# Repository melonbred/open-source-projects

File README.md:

# open-source-projects

**Repository for projects by MelonBred**

This is a repository for all open-sourced or available files for my projects. PCBs will typically have their own repository linked in the table below. Everything else will probably be found here in this repository but still linked in the tables below.

---

## Keyboards

| <div style="width:100px">_Project_</div>                                                 | _Description_                                                                                 | _Available Files_           | Image                                                                                                      |
| ---------------------------------------------------------------------------------------- | --------------------------------------------------------------------------------------------- | --------------------------- | ---------------------------------------------------------------------------------------------------------- |
| [MBLB](https://github.com/melonbred/open-source-projects/tree/main/keyboards/mblb)       | 12.5u main cluster + macro column 40% keyboard, rotary encoder support, STM32 microprocessor. | KiCAD, Gerbers, .dxf, .step |                                      |
| [MB-44](https://github.com/melonbred/open-source-projects/tree/main/keyboards/mb44)      | The MB-44 is a 12.75u layout with a fun 65%-esque blocker separating the arrow cluster.       | KiCAD, Gerbers, .dxf, .step |                                        |
| [Pegasus](https://github.com/melonbred/open-source-projects/tree/main/keyboards/pegasus) | 12.75u 40% keyboard with 0.75u "WKL" blockers                                                 | KiCAD, Gerbers, .step, .fbx |                                     |
| [MB-44 v2](https://github.com/melonbred/mb44v2/tree/main)                                | Update to the MB-44 with refreshed case and PCB.                                              | KiCAD, Gerbers, .dxf, .fbx  |  |

## PCBs

| _Project_                                                         | _Description_                                                                                                                              | _Available Files_     | Image                                                                                                        |
| ----------------------------------------------------------------- | ------------------------------------------------------------------------------------------------------------------------------------------ | --------------------- | ------------------------------------------------------------------------------------------------------------ |
| [Program Yoink!](https://github.com/melonbred/program-yoink)      | 12u main cluster with exploded arrows and macro columm                                                                                     | KiCAD, Gerbers        |    |
| [SPM1800](https://github.com/melonbred/SPM1800)                   | Southpaw compact mini 1800                                                                                                                 | KiCAD, Gerbers        |     |
| [kb-daughterboard](https://github.com/melonbred/kb-daughterboard) | USB-C daughterboard with ESD, overcurrent and overvoltage protection. 2 versions available - USB-C receptacle flush with PCB and protruded | KiCAD, Gerbers, .step |  |

## Miscellaneous

| _Project_                                                                                                  | _Description_                                       | _Available Files_ | Image                                                                                                                         |
| ---------------------------------------------------------------------------------------------------------- | --------------------------------------------------- | ----------------- | ----------------------------------------------------------------------------------------------------------------------------- |
| [MB-44 Plates](https://github.com/melonbred/open-source-projects/tree/main/miscellaneous/mb44-plate-files) | Plate files for the MB-44 keyboard                  | .dxf              |
| [Encoder Knob](https://github.com/melonbred/open-source-projects/tree/main/miscellaneous/encoder-knobs)    | Generic knob that fits EC11 encoders. 3d printable. | .step, .stl       |  |

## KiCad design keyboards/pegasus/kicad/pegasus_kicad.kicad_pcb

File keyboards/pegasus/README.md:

# pegasus

## Introduction

The Pegasus is a 12.75u layout with 0.75u "WKL" blockers.

Group buy for this keyboard ran through [P3D Store](https://p3dstore.com/) on May 21st, 2022, and all group buy orders were shipped in January, 2023. Extra units were sold on January 25th, 2023. The project was successfully completed in February, 2023.

An album of builds done by the community can be found [here](https://imgur.com/a/YTEutIl).

This repository includes kicad directory, pcb production files and case files in STEP and FBX formats.

## Features

- 12.75u layout 0.75u "WKL" blockers.
- Big bar and split bar layout options.
- Rotary encoder support.
- PCB powered by an Atmega32u4 and Unified C3 daughterboard (type-c and ESD protection) running QMK.

### KLE

## Production

Please note that the pcb production files were prepared with JLCPCB's SMT assembly in mind. Should you deicide to proceed with a different manufacturer, the Bill of Materials (BOM) and position files may need to be modified.

Vial firmware source can be found [here](https://github.com/melonbred/vial-qmk/tree/kb-pegasus/keyboards/pegasus).

Firmware is also accessible through [QMK Configurator](https://config.qmk.fm/#/pegasus/LAYOUT_default).

## Acknowledgment

This project would not have taken off without the tremendous support from the 40% keyboard community. Please feel free to join the 40% keyboard [Discord](https://discord.com/invite/40percent) server to follow up-and-coming project and join the conversations.

Thanks to [P3D Store](https://p3dstore.com/) for their support and fullfillment of the group buy!!

Thanks to all the friends that helped along the way. Y'all are the best.

This project uses repositories made available by [ai03](https://github.com/ai03-2725/).

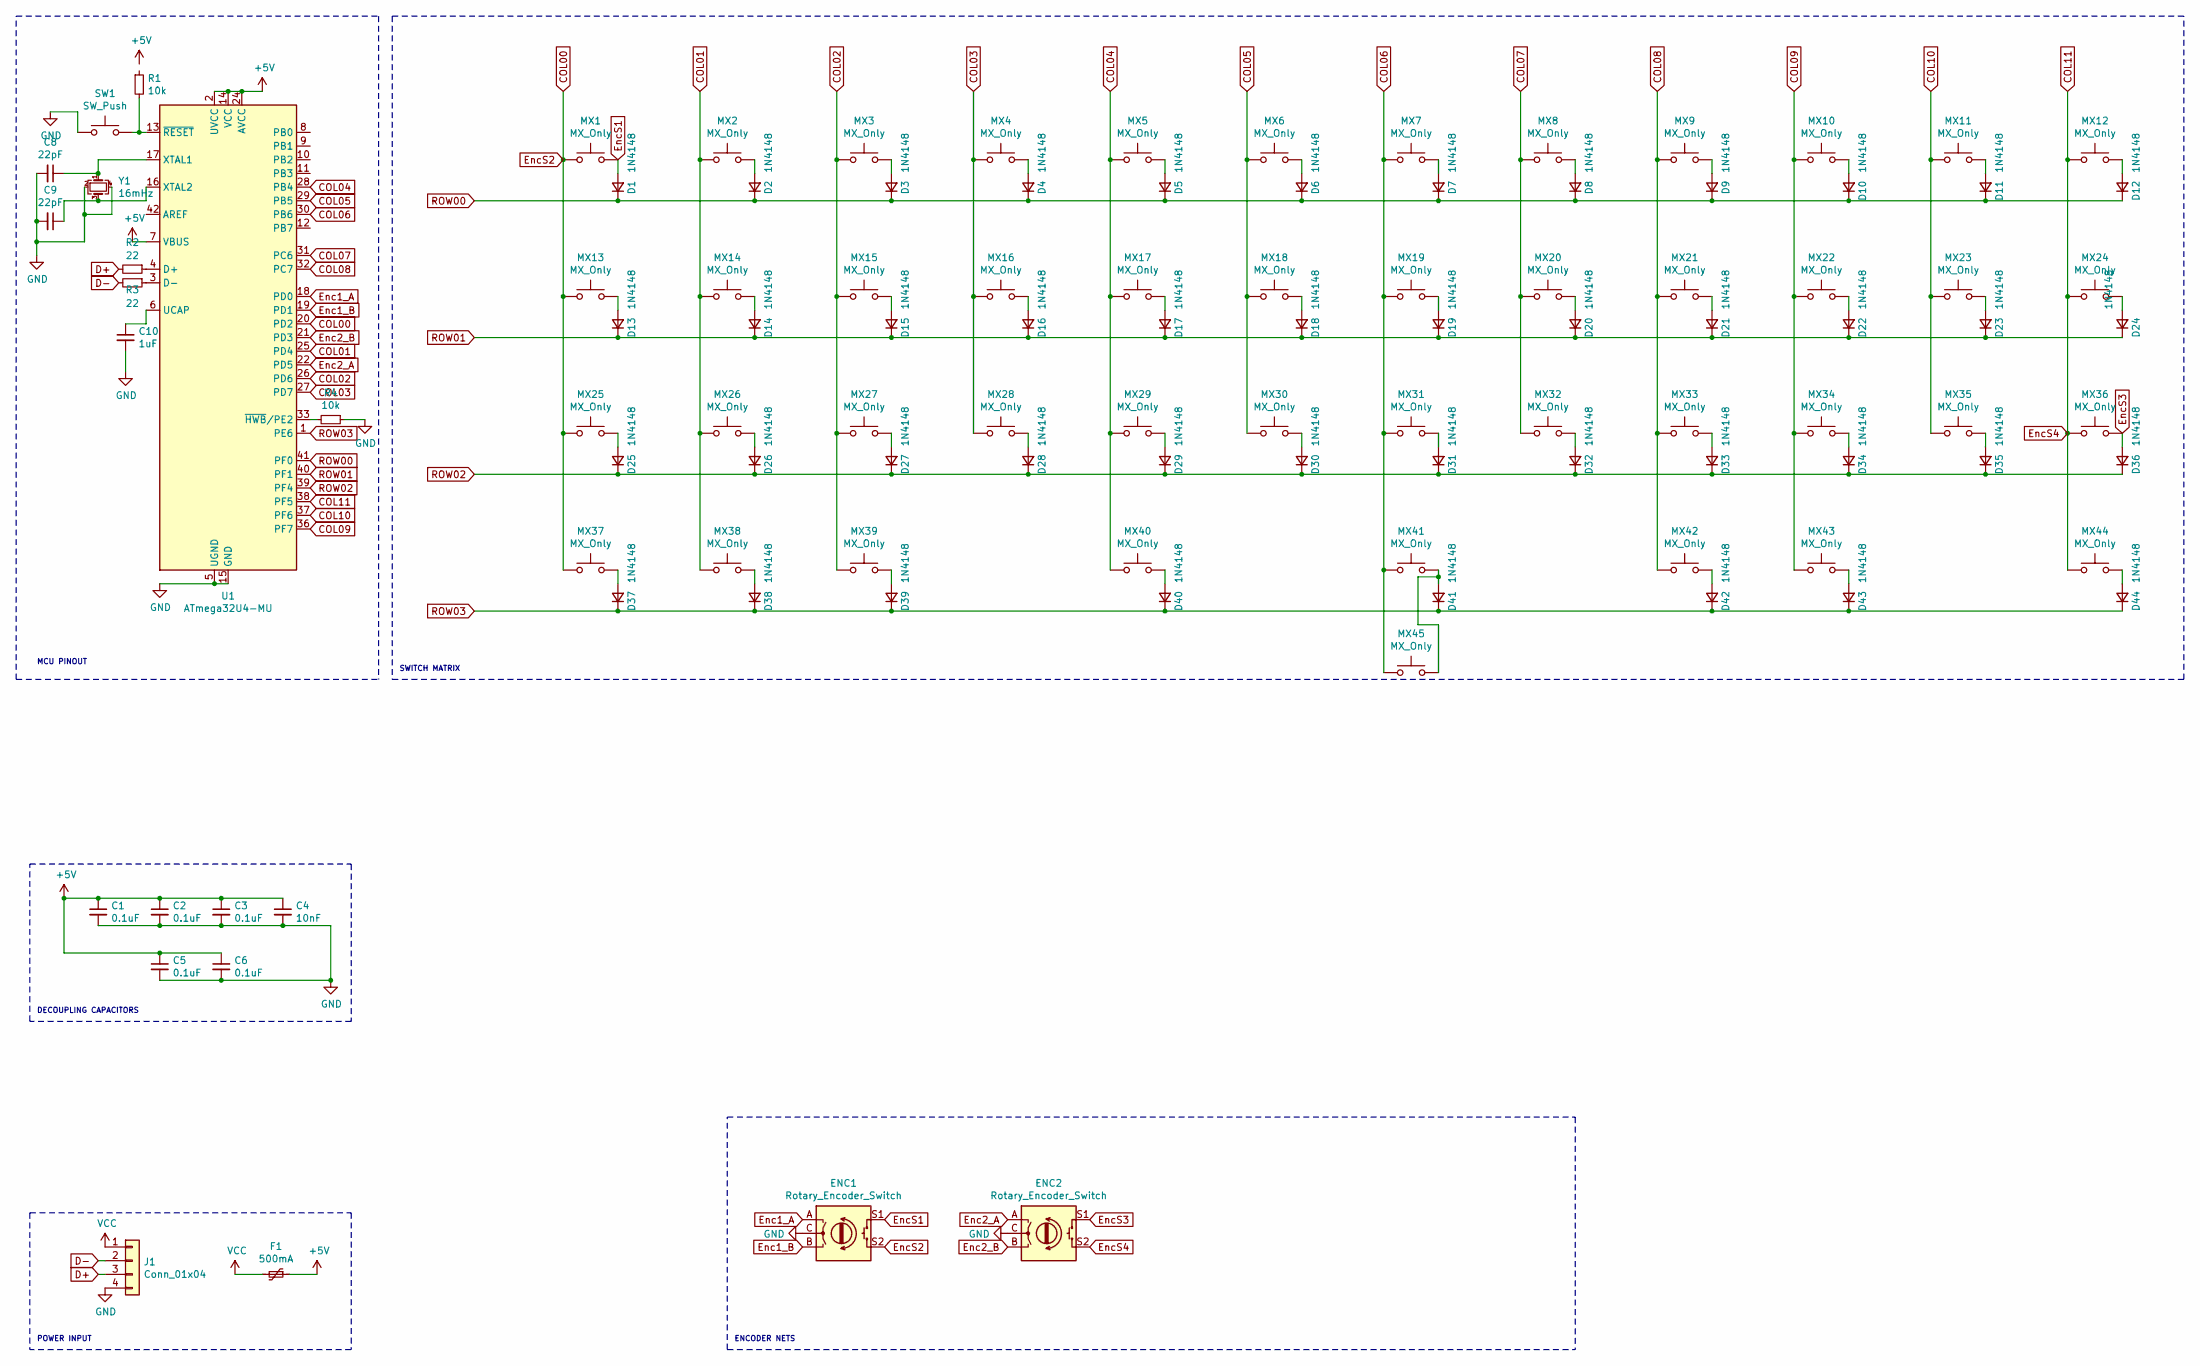
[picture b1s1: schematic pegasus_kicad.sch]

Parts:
C1, C2, C3: 0.1uF; C_0603_1608Metric; LCSC Part # C28233
C4: 10nF; C_0603_1608Metric; LCSC Part # C1710
C5, C6: 0.1uF; C_0603_1608Metric; LCSC Part # C87998
C8, C9: 22pF; C_0603_1608Metric
C10: 1uF; C_0603_1608Metric
D1, D2, D3, D4, D5, D6, D7, D8, D9, D10, D11, D12, D13, D14, D15, D16, D17, D18, D19, D20, D21, D22, D23, D24, D25, D26, D27, D28, D29, D30, D31, D32, D33, D34, D35, D36, D37, D38, D39, D40, D41, D42, D43, D44: 1N4148; D_SOD-123; LCSC Part # C402213
ENC1, ENC2: Rotary_Encoder_Switch; RotaryEncoder_Alps_EC11E-Switch_Vertical_H20mm
F1: 500mA; Fuse_1206_3216Metric; LCSC Part # C70069
J1: Conn_01x04; JST-SR-4; LCSC Part # C160404
MX1, MX2, MX3, MX4, MX5, MX6, MX7, MX8, MX9, MX10, MX11, MX14, MX15, MX16, MX17, MX18, MX19, MX20, MX21, MX22, MX23, MX26, MX27, MX28, MX29, MX30, MX31, MX32, MX33, MX34, MX35, MX36, MX39, MX42: MX_Only; MXOnly-1U-NoLED
MX12, MX25: MX_Only; MXOnly-1.75U-NoLED
MX13, MX37, MX38, MX43, MX44: MX_Only; MXOnly-1.25U-NoLED
MX24: MX_Only; MXOnly-1.5U-NoLED
MX40: MX_Only; MXOnly-2U-ReversedStabilizers-NoLED
MX41: MX_Only; MXOnly-2.25U-ReversedStabilizers-NoLED
MX45: MX_Only; MXOnly-6.25U-ReversedStabilizers-NoLED
R1, R4: 10k; R_0603_1608Metric
R2, R3: 22; R_0603_1608Metric
SW1: SW_Push; SKQG-1155865
U1: ATmega32U4-MU; QFN-44-1EP_7x7mm_P0.5mm_EP5.2x5.2mm
Y1: 16mHz; Crystal_SMD_3225-4Pin_3.2x2.5mm

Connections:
+5V: C1.1, C2.1, C3.1, C4.1, C5.1, C6.1, F1.1, U1.2 (UVCC), U1.7 (VBUS), U1.14 (VCC), U1.24 (AVCC), U1.34 (VCC), U1.44 (AVCC)
COL00: ENC1.S2, MX1.1, MX13.1, MX25.1, MX37.1, U1.20 (PD2)
COL01: MX2.1, MX14.1, MX26.1, MX38.1, U1.25 (PD4)
COL02: MX3.1, MX15.1, MX27.1, MX39.1, U1.26 (PD6)
COL03: MX4.1, MX16.1, MX28.1, U1.27 (PD7)
COL04: MX5.1, MX17.1, MX29.1, MX40.1, U1.28 (PB4)
COL05: MX6.1, MX18.1, MX30.1, U1.29 (PB5)
COL06: MX7.1, MX19.1, MX31.1, MX41.1, MX45.1, U1.30 (PB6)
COL07: MX8.1, MX20.1, MX32.1, U1.31 (PC6)
COL08: MX9.1, MX21.1, MX33.1, MX42.1, U1.32 (PC7)
COL09: MX10.1, MX22.1, MX34.1, MX43.1, U1.36 (PF7)
COL10: MX11.1, MX23.1, MX35.1, U1.37 (PF6)
COL11: ENC2.S2, MX12.1, MX24.1, MX36.1, MX44.1, U1.38 (PF5)
D+: J1.3, R2.2
D-: J1.2, R3.2
Enc1_A: ENC1.A, U1.18 (PD0)
Enc1_B: ENC1.B, U1.19 (PD1)
Enc2_A: ENC2.A, U1.22 (PD5)
Enc2_B: ENC2.B, U1.21 (PD3)
EncS1: D1.2 (A), ENC1.S1, MX1.2
EncS3: D36.2 (A), ENC2.S1, MX36.2
GND: C1.2, C2.2, C3.2, C4.2, C5.2, C6.2, C8.2, C9.2, C10.2, ENC1.C, ENC2.C, J1.4, R4.1, SW1.1, U1.5 (UGND), U1.15 (GND), U1.23 (GND), U1.35 (GND), U1.43 (GND), U1.45 (GND), Y1.2, Y1.4
unnamed: C8.1, U1.17 (XTAL1), Y1.1
unnamed: C9.1, U1.16 (XTAL2), Y1.3
unnamed: C10.1, U1.6 (UCAP)
unnamed: D2.2 (A), MX2.2
unnamed: D3.2 (A), MX3.2
unnamed: D4.2 (A), MX4.2
unnamed: D5.2 (A), MX5.2
unnamed: D6.2 (A), MX6.2
unnamed: D7.2 (A), MX7.2
unnamed: D8.2 (A), MX8.2
unnamed: D9.2 (A), MX9.2
unnamed: D10.2 (A), MX10.2
unnamed: D11.2 (A), MX11.2
unnamed: D12.2 (A), MX12.2
unnamed: D13.2 (A), MX13.2
unnamed: D14.2 (A), MX14.2
unnamed: D15.2 (A), MX15.2
unnamed: D16.2 (A), MX16.2
unnamed: D17.2 (A), MX17.2
unnamed: D18.2 (A), MX18.2
unnamed: D19.2 (A), MX19.2
unnamed: D20.2 (A), MX20.2
unnamed: D21.2 (A), MX21.2
unnamed: D22.2 (A), MX22.2
unnamed: D23.2 (A), MX23.2
unnamed: D24.2 (A), MX24.2
unnamed: D25.2 (A), MX25.2
unnamed: D26.2 (A), MX26.2
unnamed: D27.2 (A), MX27.2
unnamed: D28.2 (A), MX28.2
unnamed: D29.2 (A), MX29.2
unnamed: D30.2 (A), MX30.2
unnamed: D31.2 (A), MX31.2
unnamed: D32.2 (A), MX32.2
unnamed: D33.2 (A), MX33.2
unnamed: D34.2 (A), MX34.2
unnamed: D35.2 (A), MX35.2
unnamed: D37.2 (A), MX37.2
unnamed: D38.2 (A), MX38.2
unnamed: D39.2 (A), MX39.2
unnamed: D40.2 (A), MX40.2
unnamed: D41.2 (A), MX41.2, MX45.2
unnamed: D42.2 (A), MX42.2
unnamed: D43.2 (A), MX43.2
unnamed: D44.2 (A), MX44.2
unnamed: R1.2, SW1.2, U1.13 (~RESET)
unnamed: R2.1, U1.4 (D+)
unnamed: R3.1, U1.3 (D-)
unnamed: R4.2, U1.33 (~HWB~/PE2)
ROW00: D1.1 (K), D2.1 (K), D3.1 (K), D4.1 (K), D5.1 (K), D6.1 (K), D7.1 (K), D8.1 (K), D9.1 (K), D10.1 (K), D11.1 (K), D12.1 (K), U1.41 (PF0)
ROW01: D13.1 (K), D14.1 (K), D15.1 (K), D16.1 (K), D17.1 (K), D18.1 (K), D19.1 (K), D20.1 (K), D21.1 (K), D22.1 (K), D23.1 (K), D24.1 (K), U1.40 (PF1)
ROW02: D25.1 (K), D26.1 (K), D27.1 (K), D28.1 (K), D29.1 (K), D30.1 (K), D31.1 (K), D32.1 (K), D33.1 (K), D34.1 (K), D35.1 (K), D36.1 (K), U1.39 (PF4)
ROW03: D37.1 (K), D38.1 (K), D39.1 (K), D40.1 (K), D41.1 (K), D42.1 (K), D43.1 (K), D44.1 (K), U1.1 (PE6)
VCC: F1.2, J1.1

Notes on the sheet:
DECOUPLING CAPACITORS
POWER INPUT
ENCODER NETS
SWITCH MATRIX
MCU PINOUT

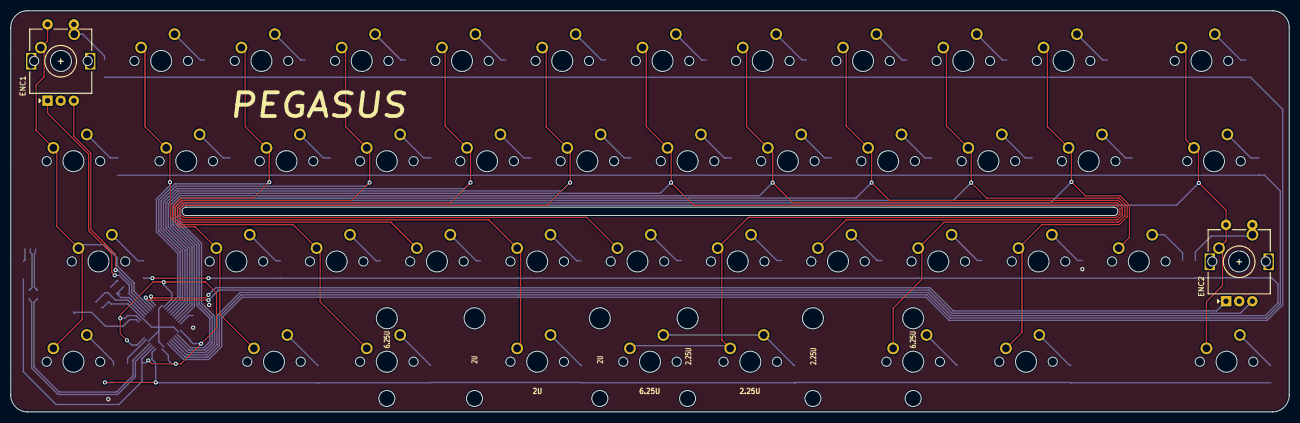
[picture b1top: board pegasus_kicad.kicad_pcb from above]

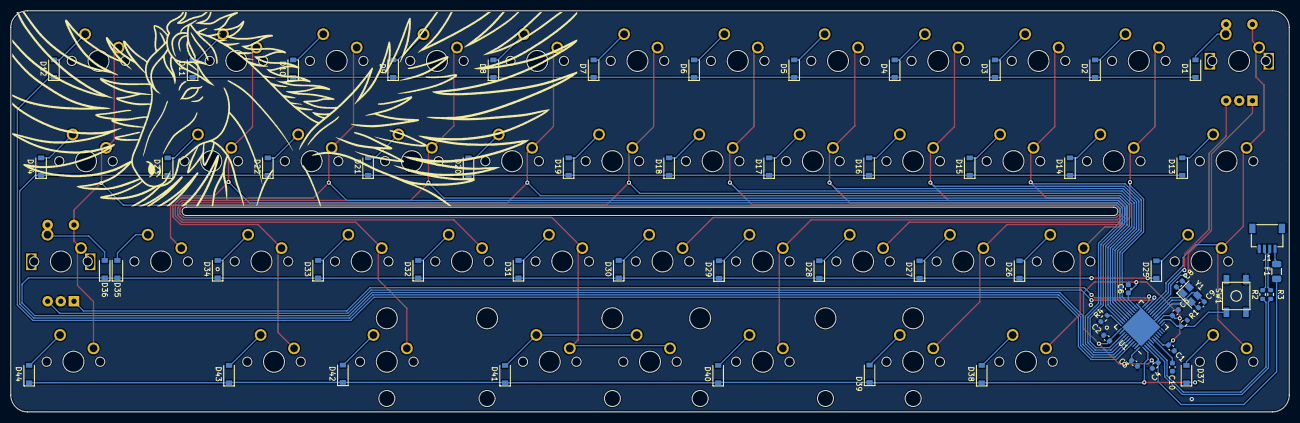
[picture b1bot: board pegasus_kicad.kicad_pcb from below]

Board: 2 copper layers, 242.9 x 76.2 mm, 109 parts (62 on the bottom side), 76 nets.

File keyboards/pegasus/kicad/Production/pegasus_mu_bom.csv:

Designator,Quantity,Value,Footprint,LCSC #
U1,1,ATmega32U4-MU,QFN-44-1EP_7x7mm_P0.5mm_EP5.2x5.2mm,C112161
"R4,R1",2,10k,R_0603_1608Metric,C25804
"D42,D25,D44,D43,D41,D40,D39,D38,D37,D36,D35,D34,D33,D32,D31,D30,D29,D28,D27,D26,D24,D23,D22,D21,D20,D19,D18,D17,D16,D15,D14,D13,D12,D11,D10,D9,D8,D7,D6,D5,D4,D3,D2,D1",44,1N4148,D_SOD-123,C64898
C10,1,1uF,C_0603_1608Metric,C15849
"C6,C5,C3,C2,C1",5,0.1uF,C_0603_1608Metric,C14663
C4,1,10nF,C_0603_1608Metric,C19702
Y1,1,16mHz,Crystal_SMD_3225-4Pin_3.2x2.5mm,C13738
SW1,1,SW_Push,SKQG-1155865,C318884
"R3,R2",2,22,R_0603_1608Metric,C23345
F1,1,500mA,Fuse_1206_3216Metric,C70076
"C9,C8",2,22pF,C_0603_1608Metric,C1653
J1,1,Conn_01x04,JST-SR-4,C160404

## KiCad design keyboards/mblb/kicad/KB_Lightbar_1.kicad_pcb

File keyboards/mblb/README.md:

# MBLB

## Introduction

This project is a 12.5u WKL main cluster + macro column 40% keyboard that was created to accomplish two goals:
- Learn about STM32 microprocessors.
- Practice trace routing with curved traces.

### KLE

### PCB

## Features
This PCB features the following:
- Powered by an STM32F072 microprocessor.
- Traditional overcharge, overcurrent and ESD protection.
- RGB LED lightbar between the macro column and 12.5u main cluster.
- Maximum of 4 rotary encoders on the macro column.

The case is a standard stacked acrylic case cut from 1.6mm sheets. The intent is to use adhere poron strips to the back of the switch plate and sandwich it between the acrylic layers above and below. However, any foam-like material would probably suffice. 

## Production
Please note that the production files were prepared with JLCPCB's SMT assembly in mind. Should you deicide to proceed with a different manufacturer, the Bill of Materials (BOM) and position files may need to be modified.

## Acknowledgment

This project uses repositories made available by [ai03](https://github.com/ai03-2725/).

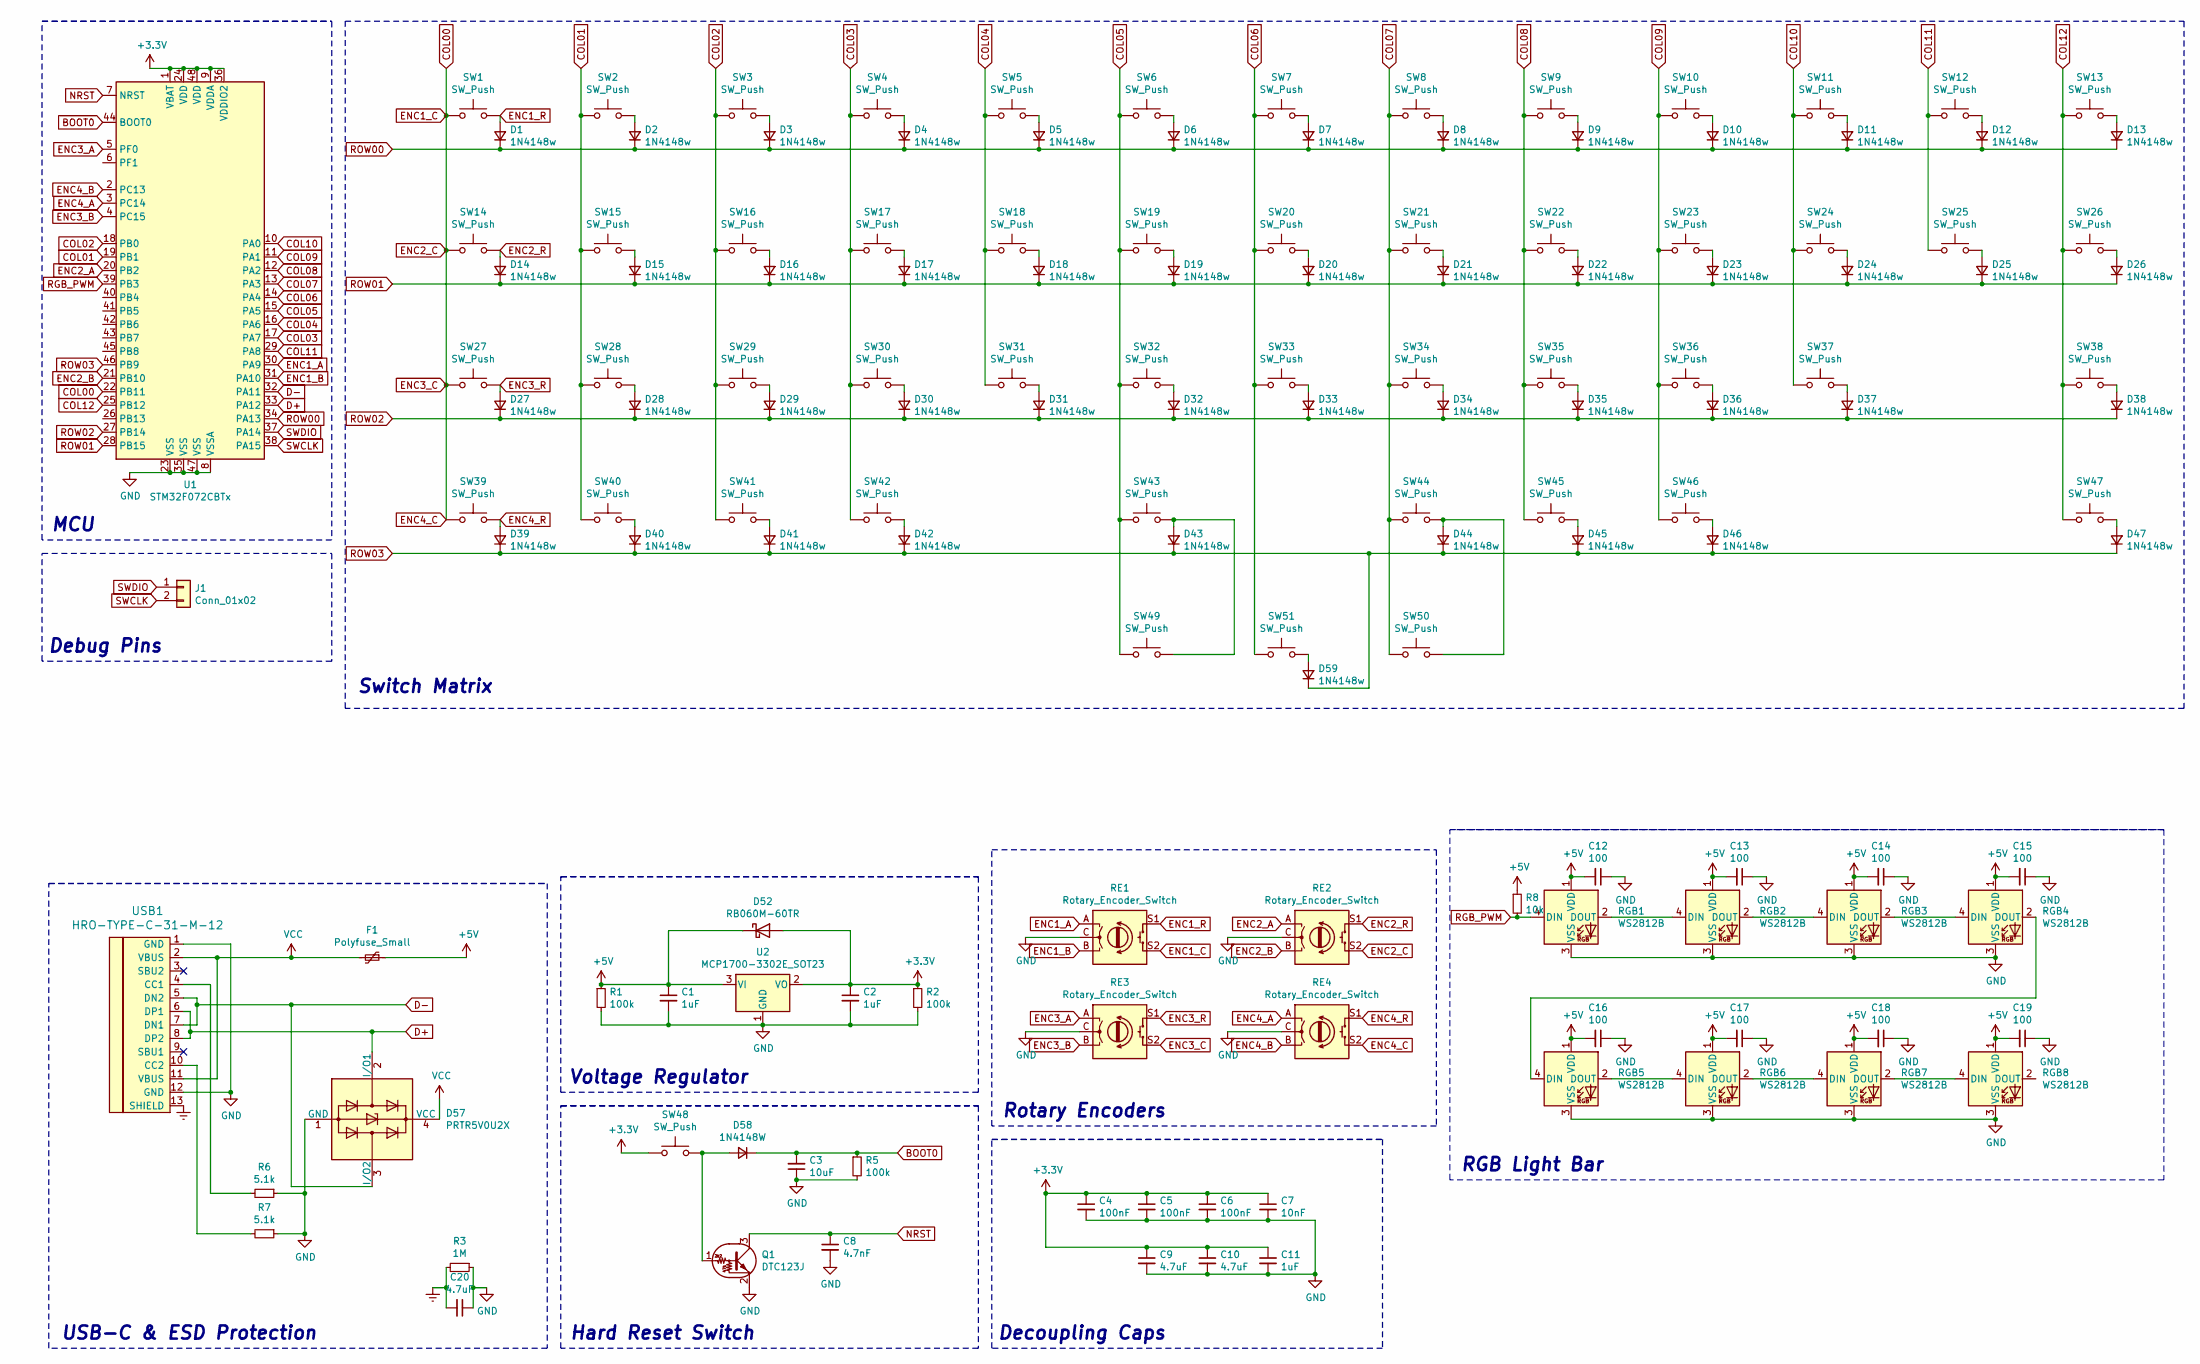
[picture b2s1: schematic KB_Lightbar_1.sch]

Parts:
C1, C2, C11: 1uF; C_0805_2012Metric
C3: 10uF; C_0805_2012Metric
C4, C5, C6: 100nF; C_0805_2012Metric
C7: 10nF; C_0805_2012Metric
C8: 4.7nF; C_0805_2012Metric
C9, C10, C20: 4.7uF; C_0805_2012Metric
C12, C13, C14, C15, C16, C17, C18, C19: 100; C_0805_2012Metric
D1, D2, D3, D4, D5, D6, D7, D8, D9, D10, D11, D12, D13, D14, D15, D16, D17, D18, D19, D20, D21, D22, D23, D24, D25, D26, D27, D28, D29, D30, D31, D32, D33, D34, D35, D36, D37, D38, D39, D40, D41, D42, D43, D44, D45, D46, D47, D59: 1N4148w; D_SOD-123
D52: RB060M-60TR; D_SOD-123
D57: PRTR5V0U2X; SOT143B
D58: 1N4148W; D_SOD-123
F1: Polyfuse_Small; Fuse_1206_3216Metric
J1: Conn_01x02; PinHeader_1x02_P2.54mm_Vertical
Q1: DTC123J; SOT-23
R1, R2, R5: 100k; R_0805_2012Metric
R3: 1M; R_0805_2012Metric
R6, R7: 5.1k; R_0805_2012Metric
R8: 10k; R_0805_2012Metric
RE1, RE2, RE3, RE4: Rotary_Encoder_Switch; RotaryEncoder_Alps_EC11E-Switch_Vertical_H20mm
RGB1, RGB2, RGB3, RGB4, RGB5, RGB6, RGB7, RGB8: WS2812B; LED_WS2812B_PLCC4_5.0x5.0mm_P3.2mm
SW1, SW2, SW3, SW4, SW5, SW6, SW7, SW8, SW9, SW10, SW11, SW12, SW14, SW16, SW17, SW18, SW19, SW20, SW21, SW22, SW23, SW24, SW25, SW27, SW29, SW30, SW31, SW32, SW33, SW34, SW35, SW36, SW37, SW39, SW42, SW45: SW_Push; MXOnly-1U-NoLED
SW13: SW_Push; MXOnly-1.5U-NoLED
SW15, SW26, SW40, SW41, SW46, SW47: SW_Push; MXOnly-1.25U-NoLED
SW28, SW38: SW_Push; MXOnly-1.75U-NoLED
SW43, SW44: SW_Push; MXOnly-2U-ReversedStabilizers-NoLED
SW48: SW_Push; SKQG-1155865
SW49, SW50: SW_Push; MXOnly-3U-ReversedStabilizers-NoLED
SW51: SW_Push; MXOnly-6U-Centered-ReversedStabilizers-NoLED
U1: STM32F072CBTx; LQFP-48_7x7mm_P0.5mm
U2: MCP1700-3302E_SOT23; SOT-23
USB1: HRO-TYPE-C-31-M-12; HRO-TYPE-C-31-M-12-HandSoldering

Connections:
+3V3: C2.1, C4.1, C5.1, C6.1, C7.1, C9.1, C10.1, C11.1, D52.2 (A), R2.1, SW48.1, U1.1 (VBAT), U1.9 (VDDA), U1.24 (VDD), U1.36 (VDDIO2), U1.48 (VDD), U2.2 (VO)
+5V: C1.1, C12.2, C13.2, C14.2, C15.2, C16.2, C17.2, C18.2, C19.2, D52.1 (K), F1.1, R1.1, R8.1, RGB1.1 (VDD), RGB2.1 (VDD), RGB3.1 (VDD), RGB4.1 (VDD), RGB5.1 (VDD), RGB6.1 (VDD), RGB7.1 (VDD), RGB8.1 (VDD), U2.3 (VI)
BOOT0: C3.2, D58.1 (K), R5.1, U1.44 (BOOT0)
COL00: RE1.S2, RE2.S2, RE3.S2, RE4.S2, SW1.1, SW14.1, SW27.1, SW39.1, U1.22 (PB11)
COL01: SW2.1, SW15.1, SW28.1, SW40.1, U1.19 (PB1)
COL02: SW3.1, SW16.1, SW29.1, SW41.1, U1.18 (PB0)
COL03: SW4.1, SW17.1, SW30.1, SW42.1, U1.17 (PA7)
COL04: SW5.1, SW18.1, SW31.1, U1.16 (PA6)
COL05: SW6.1, SW19.1, SW32.1, SW43.1, SW49.1, U1.15 (PA5)
COL06: SW7.1, SW20.1, SW33.1, SW51.1, U1.14 (PA4)
COL07: SW8.1, SW21.1, SW34.1, SW44.1, SW50.1, U1.13 (PA3)
COL08: SW9.1, SW22.1, SW35.1, SW45.1, U1.12 (PA2)
COL09: SW10.1, SW23.1, SW36.1, SW46.1, U1.11 (PA1)
COL10: SW11.1, SW24.1, SW37.1, U1.10 (PA0)
COL11: SW12.1, SW25.1, U1.29 (PA8)
COL12: SW13.1, SW26.1, SW38.1, SW47.1, U1.25 (PB12)
D+: D57.2 (I/O1), U1.33 (PA12), USB1.6 (DP1), USB1.8 (DP2)
D-: D57.3 (I/O2), U1.32 (PA11), USB1.5 (DN2), USB1.7 (DN1)
ENC1_A: RE1.A, U1.30 (PA9)
ENC1_B: RE1.B, U1.31 (PA10)
ENC1_R: D1.2 (A), RE1.S1, SW1.2
ENC2_A: RE2.A, U1.20 (PB2)
ENC2_B: RE2.B, U1.21 (PB10)
ENC2_R: D14.2 (A), RE2.S1, SW14.2
ENC3_A: RE3.A, U1.5 (PF0)
ENC3_B: RE3.B, U1.4 (PC15)
ENC3_R: D27.2 (A), RE3.S1, SW27.2
ENC4_A: RE4.A, U1.3 (PC14)
ENC4_B: RE4.B, U1.2 (PC13)
ENC4_R: D39.2 (A), RE4.S1, SW39.2
Earth: C20.2, R3.2, USB1.13 (SHIELD)
GND: C1.2, C2.2, C3.1, C4.2, C5.2, C6.2, C7.2, C8.2, C9.2, C10.2, C11.2, C12.1, C13.1, C14.1, C15.1, C16.1, C17.1, C18.1, C19.1, C20.1, D57.1 (GND), Q1.2 (E), R1.2, R2.2, R3.1, R5.2, R6.1, R7.1, RE1.C, RE2.C, RE3.C, RE4.C, RGB1.3 (VSS), RGB2.3 (VSS), RGB3.3 (VSS), RGB4.3 (VSS), RGB5.3 (VSS), RGB6.3 (VSS), RGB7.3 (VSS), RGB8.3 (VSS), U1.8 (VSSA), U1.23 (VSS), U1.35 (VSS), U1.47 (VSS), U2.1 (GND), USB1.1 (GND), USB1.12 (GND)
NRST: C8.1, Q1.3 (C), U1.7 (NRST)
unnamed: D2.2 (A), SW2.2
unnamed: D3.2 (A), SW3.2
unnamed: D4.2 (A), SW4.2
unnamed: D5.2 (A), SW5.2
unnamed: D6.2 (A), SW6.2
unnamed: D7.2 (A), SW7.2
unnamed: D8.2 (A), SW8.2
unnamed: D9.2 (A), SW9.2
unnamed: D10.2 (A), SW10.2
unnamed: D11.2 (A), SW11.2
unnamed: D12.2 (A), SW12.2
unnamed: D13.2 (A), SW13.2
unnamed: D15.2 (A), SW15.2
unnamed: D16.2 (A), SW16.2
unnamed: D17.2 (A), SW17.2
unnamed: D18.2 (A), SW18.2
unnamed: D19.2 (A), SW19.2
unnamed: D20.2 (A), SW20.2
unnamed: D21.2 (A), SW21.2
unnamed: D22.2 (A), SW22.2
unnamed: D23.2 (A), SW23.2
unnamed: D24.2 (A), SW24.2
unnamed: D25.2 (A), SW25.2
unnamed: D26.2 (A), SW26.2
unnamed: D28.2 (A), SW28.2
unnamed: D29.2 (A), SW29.2
unnamed: D30.2 (A), SW30.2
unnamed: D31.2 (A), SW31.2
unnamed: D32.2 (A), SW32.2
unnamed: D33.2 (A), SW33.2
unnamed: D34.2 (A), SW34.2
unnamed: D35.2 (A), SW35.2
unnamed: D36.2 (A), SW36.2
unnamed: D37.2 (A), SW37.2
unnamed: D38.2 (A), SW38.2
unnamed: D40.2 (A), SW40.2
unnamed: D41.2 (A), SW41.2
unnamed: D42.2 (A), SW42.2
unnamed: D43.2 (A), SW43.2, SW49.2
unnamed: D44.2 (A), SW44.2, SW50.2
unnamed: D45.2 (A), SW45.2
unnamed: D46.2 (A), SW46.2
unnamed: D47.2 (A), SW47.2
unnamed: D58.2 (A), Q1.1 (B), SW48.2
unnamed: D59.2 (A), SW51.2
unnamed: R6.2, USB1.4 (CC1)
unnamed: R7.2, USB1.10 (CC2)
unnamed: RGB1.2 (DOUT), RGB2.4 (DIN)
unnamed: RGB2.2 (DOUT), RGB3.4 (DIN)
unnamed: RGB3.2 (DOUT), RGB4.4 (DIN)
unnamed: RGB4.2 (DOUT), RGB5.4 (DIN)
unnamed: RGB5.2 (DOUT), RGB6.4 (DIN)
unnamed: RGB6.2 (DOUT), RGB7.4 (DIN)
unnamed: RGB7.2 (DOUT), RGB8.4 (DIN)
RGB_PWM: R8.2, RGB1.4 (DIN), U1.39 (PB3)
ROW00: D1.1 (K), D2.1 (K), D3.1 (K), D4.1 (K), D5.1 (K), D6.1 (K), D7.1 (K), D8.1 (K), D9.1 (K), D10.1 (K), D11.1 (K), D12.1 (K), D13.1 (K), U1.34 (PA13)
ROW01: D14.1 (K), D15.1 (K), D16.1 (K), D17.1 (K), D18.1 (K), D19.1 (K), D20.1 (K), D21.1 (K), D22.1 (K), D23.1 (K), D24.1 (K), D25.1 (K), D26.1 (K), U1.28 (PB15)
ROW02: D27.1 (K), D28.1 (K), D29.1 (K), D30.1 (K), D31.1 (K), D32.1 (K), D33.1 (K), D34.1 (K), D35.1 (K), D36.1 (K), D37.1 (K), D38.1 (K), U1.27 (PB14)
ROW03: D39.1 (K), D40.1 (K), D41.1 (K), D42.1 (K), D43.1 (K), D44.1 (K), D45.1 (K), D46.1 (K), D47.1 (K), D59.1 (K), U1.46 (PB9)
SWCLK: J1.2, U1.38 (PA15)
SWDIO: J1.1, U1.37 (PA14)
VCC: D57.4 (VCC), F1.2, USB1.2 (VBUS), USB1.11 (VBUS)

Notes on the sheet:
Decoupling Caps
Hard Reset Switch
USB-C & ESD Protection
Voltage Regulator
Switch Matrix
MCU
Rotary Encoders
Debug Pins
RGB Light Bar

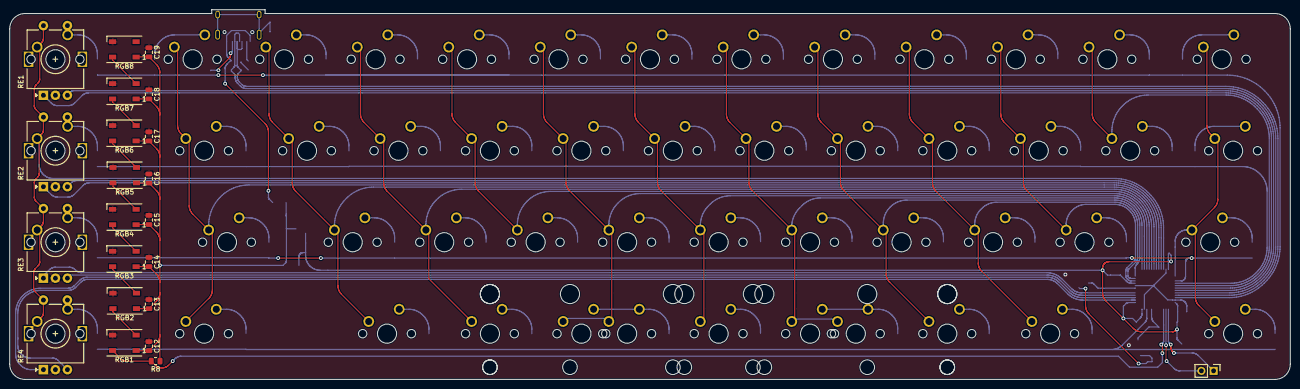
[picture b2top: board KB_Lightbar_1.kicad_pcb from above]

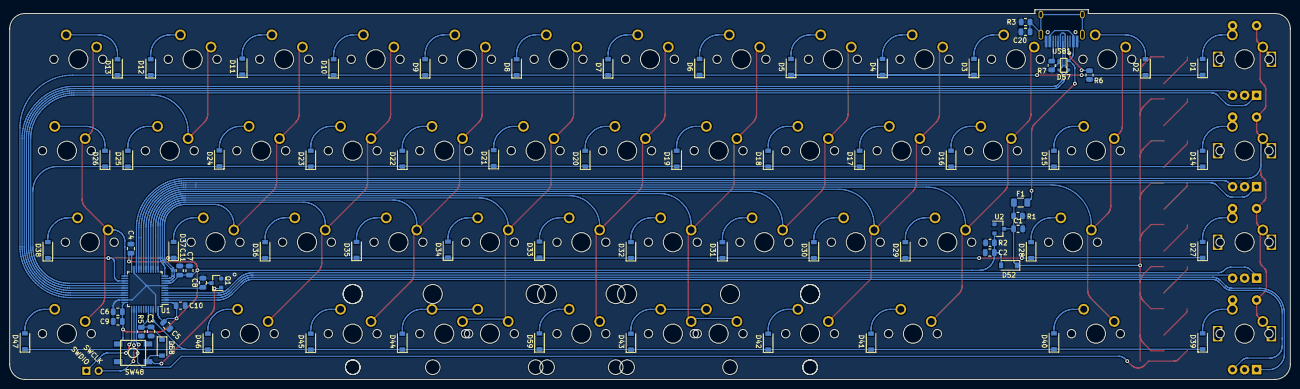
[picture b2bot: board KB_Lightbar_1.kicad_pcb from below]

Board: 2 copper layers, 266.7 x 77.0 mm, 147 parts (75 on the bottom side), 95 nets.

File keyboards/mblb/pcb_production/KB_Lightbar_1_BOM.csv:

Designator, Quantity, Value, Footprint,LCSC Part #
C1 C2 C11 ,2,1uF,Capacitor_SMD:C_0805_2012Metric,C24123
C3 ,1,10uF,Capacitor_SMD:C_0805_2012Metric,C95841
C4 C5 C6 ,3,100nF,Capacitor_SMD:C_0805_2012Metric,C28233
C7 ,1,10nF,Capacitor_SMD:C_0805_2012Metric,C1710
C8 ,1,4.7nF,Capacitor_SMD:C_0805_2012Metric,C21217
C9 C10 C20 ,3,4.7uF,Capacitor_SMD:C_0805_2012Metric,C87998
D1 D2 D3 D4 D5 D6 D7 D8 D9 D10 D11 D12 D13 D14 D15 D16 D17 D18 D19 D20 D21 D22 D23 D24 D25 D26 D27 D28 D29 D30 D31 D32 D33 D34 D35 D36 D37 D38 D39 D40 D41 D42 D43 D44 D45 D46 D47 D59 ,48,1N4148w,Diode_SMD:D_SOD-123,C402213
D52 ,1,RB060M-60TR,Diode_SMD:D_SOD-123,C114257
D57 ,1,PRTR5V0U2X,random-keyboard-parts:SOT143B,C12333
D58 ,1,1N4148W,Diode_SMD:D_SOD-123,C402213
F1 ,1,Polyfuse_Small,Fuse:Fuse_1206_3216Metric,C70069
Q1 ,1,DTC123J,Package_TO_SOT_SMD:SOT-23,C406040
R3 ,1,1M,Resistor_SMD:R_0805_2012Metric,C269728
R1 R2 R5 ,3,100k,Resistor_SMD:R_0805_2012Metric,C406726
R6 R7 ,2,5.1k,Resistor_SMD:R_0805_2012Metric,C328405
R8 ,1,10k,Resistor_SMD:R_0805_2012Metric,C365230
SW48 ,1,SW_Push,random-keyboard-parts:SKQG-1155865,C318884
U1 ,1,STM32F072CBTx,Package_QFP:LQFP-48_7x7mm_P0.5mm,C81720
U2 ,1,MCP1700-3302E_SOT23,Package_TO_SOT_SMD:SOT-23,C39051
USB1 ,1,HRO-TYPE-C-31-M-12,Type-C:HRO-TYPE-C-31-M-12-HandSoldering,C165948

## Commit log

2021-05-16 Added knob files
2021-05-17 Added readme
2022-02-02 Added kb-daughterboard project
2022-02-03 added mblb
2022-02-03 moved image
2022-02-05 added mb44
2022-02-05 add mb44
2022-02-11 added firmware
2023-03-14 added pegasus pcb
2024-07-14 Add Pegasus folder
2024-07-14 README update
2026-03-03 Add mb44v2 to README.md
